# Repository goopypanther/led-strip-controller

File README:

Control board for individually addressable RGB LED strip, such as
https://www.adafruit.com/products/306
or other cheap chinese knockoffs.

Features:
 * 16MHz Atmega168
 * Onboard microphone connected to ADC
 * Debug LED
 * Hardware SPI breakout
 * FTDI ttl programming header

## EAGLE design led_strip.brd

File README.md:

Control board for individually addressable RGB LED strip, such as
https://www.adafruit.com/products/306
or other cheap chinese knockoffs.

Features:
 * 5V power regulator
 * 16MHz Atmega168
 * Onboard microphone connected to ADC
 * Debug LED
 * Hardware SPI breakout
 * FTDI ttl programming header

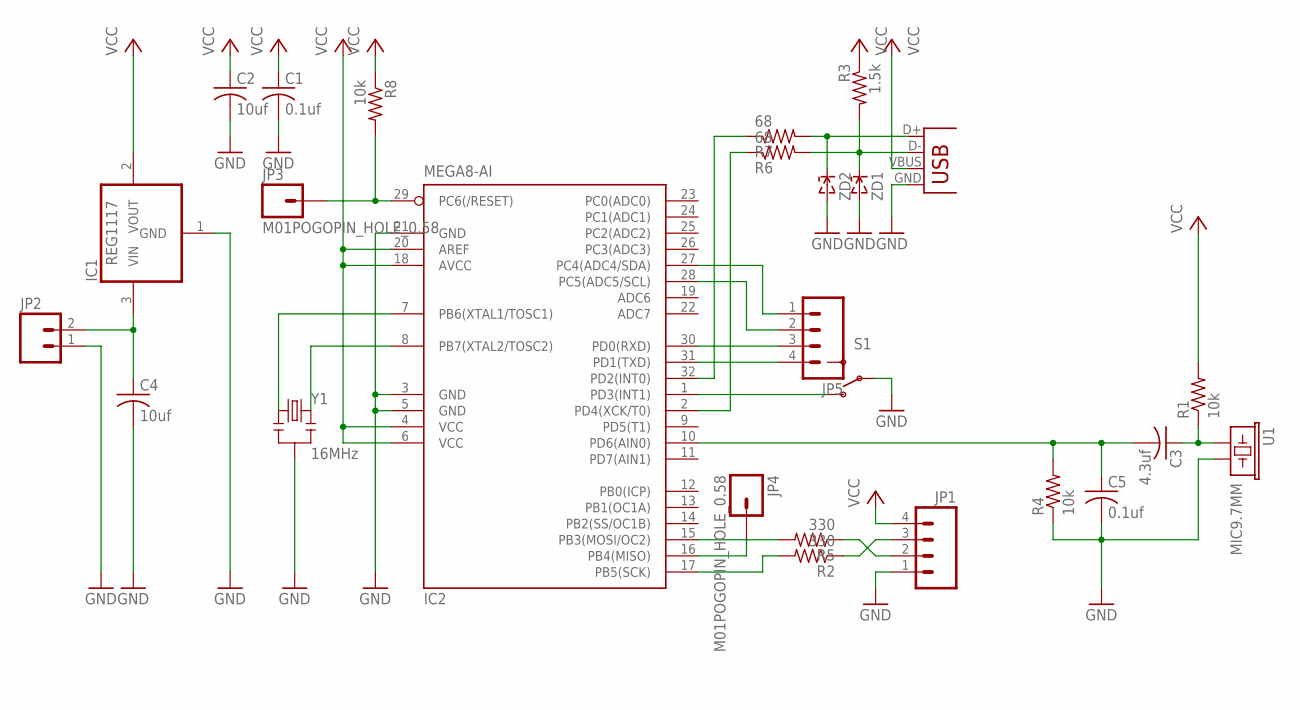
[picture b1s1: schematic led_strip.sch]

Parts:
C1, C5: 0.1uf; C0805
C2, C4: 10uf; C0805
C3: 4.3uf; C0805
IC1: REG1117; SOT223
IC2: MEGA8-AI; TQFP32-08
JP1: M04LONGPADS; 1X04_LONGPADS
JP2: M02LOCK_LONGPADS; 1X02_LOCK_LONGPADS
JP3, JP4: M01POGOPIN_HOLE_0.58; 1X01_POGOPIN_HOLE_0.58
JP5: M04PTH; 1X04
R1, R4, R8: 10k; R0805
R2, R5: 330; R0805
R3: 1.5k; R0805
R6, R7: 68; R0805
S1: SWITCH-SPSTSMD2; SWITCH-SPDT-SMD
U1: MIC9.7MM; MIC-9.7MM
X1: USB-SMD-NS; USB-MINIB-NOSTOP
Y1: 16MHz; RESONATOR-SMD
ZD1, ZD2: ZENERSOD-323F; SOD-323F

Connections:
GND: C1.2, C2.2, C4.2, C5.2, IC1.1 (GND), IC2.3 (GND), IC2.5 (GND), IC2.21 (GND), JP1.1, JP2.1, R4.1, S1.2, U1.2, X1.GND, Y1.2, ZD1.A, ZD2.A
unnamed: IC2.17 (PB5(SCK)), R2.2
unnamed: IC2.16 (PB4(MISO)), JP4.1
unnamed: JP1.2, R5.1
unnamed: R7.2, X1.D+, ZD2.C
unnamed: R3.2, R6.2, X1.D-, ZD1.C
unnamed: IC2.7 (PB6(XTAL1/TOSC1)), Y1.1
unnamed: IC2.29 (PC6(/RESET)), JP3.1, R8.2
unnamed: IC2.8 (PB7(XTAL2/TOSC2)), Y1.3
unnamed: C3.2, C5.1, IC2.10 (PD6(AIN0)), R4.2
unnamed: C3.1, R1.1, U1.1
unnamed: IC2.2 (PD4(XCK/T0)), R6.1
unnamed: IC2.32 (PD2(INT0)), R7.1
unnamed: IC2.1 (PD3(INT1)), S1.1 (O)
unnamed: JP1.3, R2.1
unnamed: IC2.15 (PB3(MOSI/OC2)), R5.2
unnamed: IC2.30 (PD0(RXD)), JP5.3
unnamed: IC2.31 (PD1(TXD)), JP5.4
unnamed: IC2.28 (PC5(ADC5/SCL)), JP5.2
unnamed: IC2.27 (PC4(ADC4/SDA)), JP5.1
unnamed: C4.1, IC1.3 (VIN), JP2.2
VCC: C1.1, C2.1, IC1.2 (VOUT), IC2.4 (VCC), IC2.6 (VCC), IC2.18 (AVCC), IC2.20 (AREF), JP1.4, R1.2, R3.1, R8.1, X1.VBUS

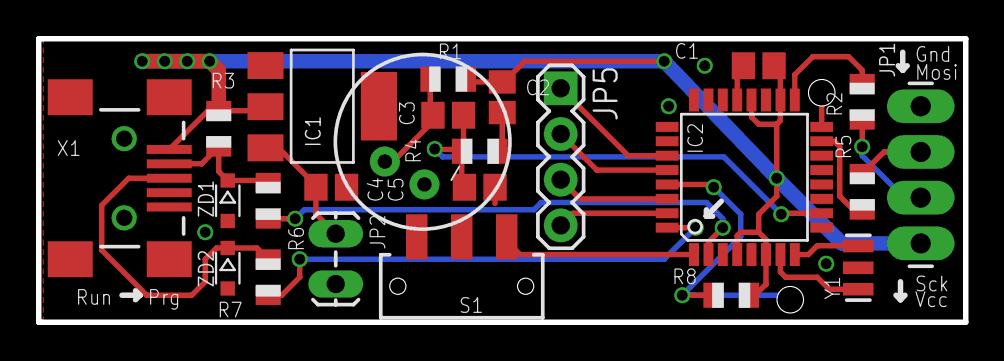
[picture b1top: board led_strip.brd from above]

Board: 2 copper layers, 51.5 x 15.8 mm, 26 parts (0 on the bottom side), 22 nets.

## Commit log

2013-01-13 Commited everything, probably should have been doing this as I worked. >.>;
2013-01-13 Fixed spelling error
2013-01-13 renamed readme for markdown
2013-03-31 Added DTR capacitor for programming, reversed SPI header for LED stip.
2013-03-31 Updated BOM, fixed LED current limiting resistor to sane value.
2013-03-31 Update README.md
    Fixed image tags
2013-03-31 Update README.md
    Re-fixed image tags.
2013-04-07 Created usb bootloader varient.
2013-04-18 Fixed up layout for ordering.
2014-03-27 added gitignore for save files
2014-03-27 still adding io pins, fixed mic input issue

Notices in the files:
parts and their libraries:
sparkfun: Licensing: CC v3.0 Share-Alike You are welcome to use this library for commercial purposes.
